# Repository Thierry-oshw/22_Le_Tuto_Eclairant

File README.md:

# 22_Le_Tuto_Eclairant

 mots clés: tutoriel led rgb éclairage diorama lighting

## Introduction

Les LEDs sont utilisables pour un diorama. Elles présentent comme avantages:
    1. De ne pas chauffer (en tout cas moins qu’une ampoule si ça existe encore).
    2. D’être tellement vulgarisées et diffusées que leur coût est très faible.
    3. De fonctionner sous une faible tension (de l’ordre de 1,2V pour les LEDs classiques et 5V pour les RGBs)

Une LED RGB est la somme de 3 leds (Rouge, Verte, Bleue = Red Green Blue) pilotées par une petite puce qui va recevoir des instructions par une patte et les retransmettre par une autre pour la LED RGB suivante. Ce point va être détaillé par la suite.

Petite photo de famille :

En gros, LED classique = 2 pattes, LED RGB = 4 pattes.
Il y a aussi des LEDs classiques bicolores (il y a deux LEDs de couleurs différentes dans le même bulb). Mais je ne vais pas approfondir ce sujet là.

## Pilotage d’une LED classique

Il faut alimenter la LED classique avec une tension à ses bornes de 1,2V en général, et contrôler le courant qui y circule pour qu’il soit de l’ordre de 10mA (entre 5 et 20mA).
Plus le courant est fort, plus la luminosité est forte.
Pour obtenir ces conditions, le plus simple est de relier la LED classique à une source de tension via une résistance qui va limiter le courant et faire chuter la tension.

Et en gros, pour ceux qui s’en souvienne : u = R1 * i + u(diode)
U(diode) vaut approximativement 1,2V. Si i vaut 5mA, il faut les couples suivants tension u et résistance R1 (je suis sympa, je vous fais un tableau avec des valeurs normalisées).

|u|i|
|-|:-|
|1,5V (pile AAA cylindrique par exemple)|68 Ohms|
|3,3V|470 Ohms|
|5V|820 Ohms|

Les résistances devront avoir un boîtier permettant de dissiper au moins 50mW.
ATTENTION : toujours mettre une résistance sinon ça va mal finir pour la LED. (il y a une façon de faire pour ne pas mettre de résistance mais il faut alors piloter la LED en courant, c’est pas simple).

## Pilotage LED RGB

Il y a plusieurs fabricants de LED RGBs avec bien sûr des différences. Je sais faire fonctionner des LEDs WS2812B (et apparentés). Donc je vous parle de celles-ci.

Là, la LED a besoin d’une tension 5V sur les pattes 1 (VDD au plus) et 3 (VSS au moins).
La patte DIN reçoit les ordres pour les 3 couleurs pour elle-même ou la suivante via sa patte DOUT.
Les LEDS sont à la queue-leu-leu (daisy chain en anglais).

Une méthode pour les piloter est alors d’utiliser par exemple une carte Arduino Nano avec 3 potentiomètres par exemple :

Et on utilise le bouton pour régler l'intensité lumineuse.

Les potentiomètres sont dédiées chacun à l'intensité d'une couleur.

La brillance de l'ensemble est réglée par un bouton. Un appui long fait augmenter la valeur jusqu'à un max et retombe à zéro.

Le code arduino est dans le répertoire: Le_Tuto_Eclairant_SW de ce projet.
J'ai utilisé Visual Studio Code avec platform IO. Vous pouvez utilisez à la place l'IDE arduino, vous avez juste à recopier le fichier main dans:
\Le_Tuto_Eclairant_SW\Le_Tuto_Eclairant_SW\src\main.cpp
et le renommer en .ino ou le coller dans un projet Arduino.

Le code est très simple. (Je n'ai même pas mis de debounce sur le bouton..)

Le projet kicad est dans le répertoire: Le_Tuto_Eclairant_HW.
J'utilise encore Kicad version 5, j'ai pas encore migré.

Les fichiers pour la fabrication du PCB sont dans le répertoire: Le_Tuto_Eclairant_HW\dossier_fabrication
Ils sont prêts pour être fabriqué chez JLCPCB.COM. (C'est un exemple).

Quelques photos du résultat:

En espérant que cela puisse vous permettre de réaliser un diorama avec la lumière qui vous plait.

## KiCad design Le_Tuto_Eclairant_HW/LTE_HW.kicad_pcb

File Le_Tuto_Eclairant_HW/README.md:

# Le_Tuto_Eclairant_HW
 Hardware du Tuto éclairant.

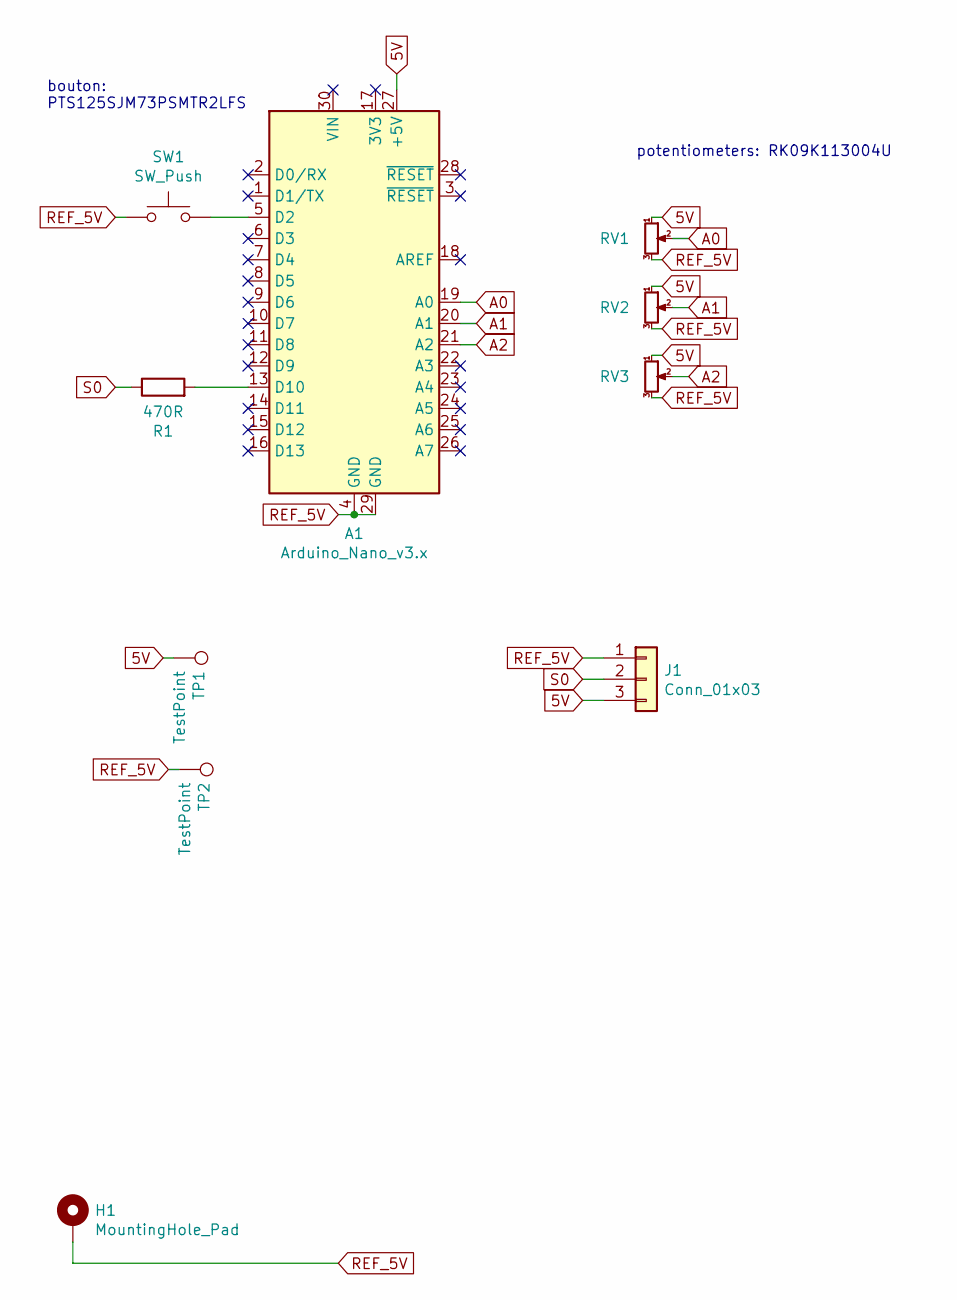
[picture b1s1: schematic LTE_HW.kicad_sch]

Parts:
A1: Arduino_Nano_v3.x; Arduino_Nano
H1: MountingHole_Pad; MountingHole_3.2mm_M3_Pad_Via
J1: Conn_01x03; JST_XH_S3B-XH-A_1x03_P2.50mm_Horizontal
R1: 470R; R_0603_1608Metric_Pad1.05x0.95mm_HandSolder
RV1, RV2, RV3: R_Potentiometer_Small; Potentiometer_Alps_RK09K_Single_Vertical
SW1: SW_Push; SW_Push_1P1T_NO_CK_PTS125Sx43PSMTR
TP1, TP2: TestPoint; PinHeader_1x01_P2.54mm_Vertical

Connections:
5V: A1.27 (+5V), J1.3, RV1.1, RV2.1, RV3.1, TP1.1
A0: A1.19 (A0), RV1.2
A1: A1.20 (A1), RV2.2
A2: A1.21 (A2), RV3.2
unnamed: A1.5 (D2), SW1.2
unnamed: A1.13 (D10), R1.2
REF_5V: A1.4 (GND), A1.29 (GND), H1.1, J1.1, RV1.3, RV2.3, RV3.3, SW1.1, TP2.1
S0: J1.2, R1.1

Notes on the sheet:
bouton: PTS125SJM73PSMTR2LFS
potentiometers: RK09K113004U

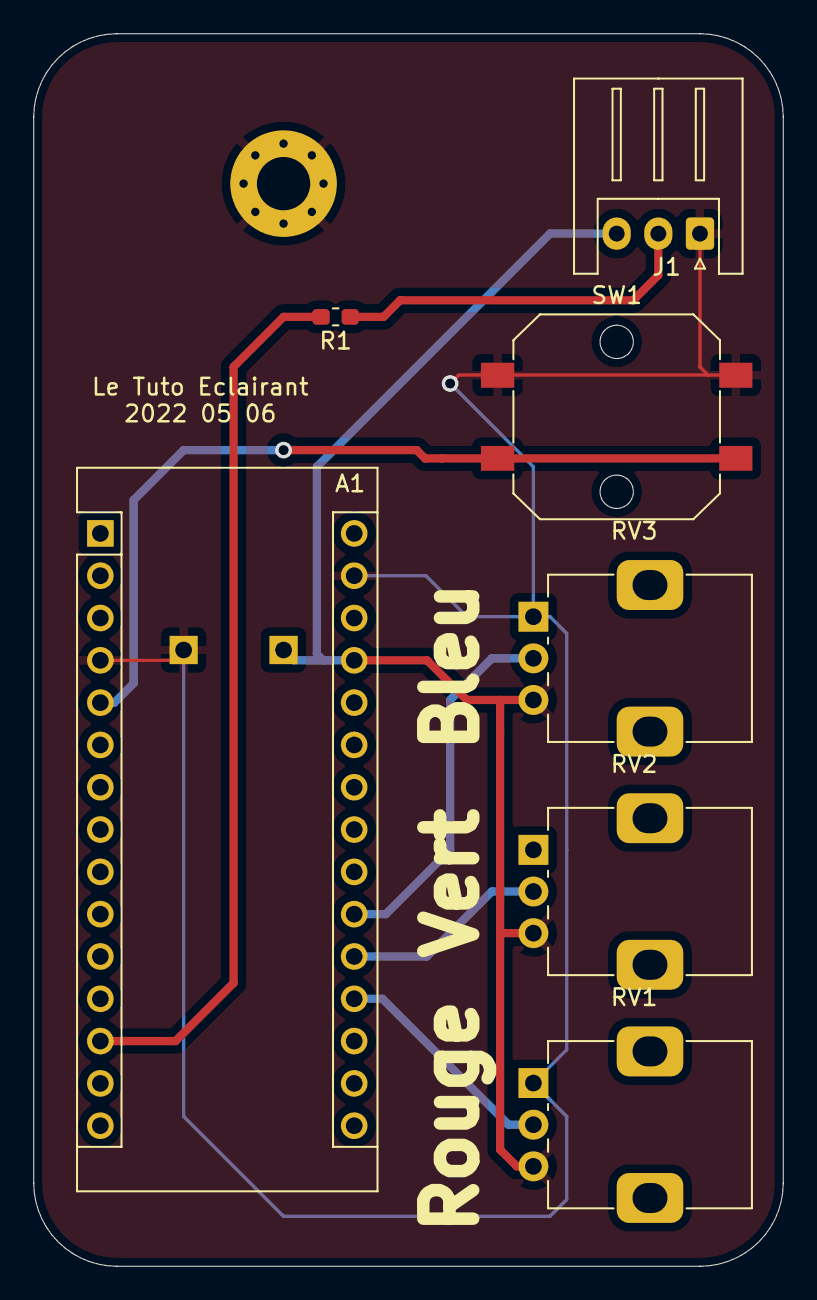
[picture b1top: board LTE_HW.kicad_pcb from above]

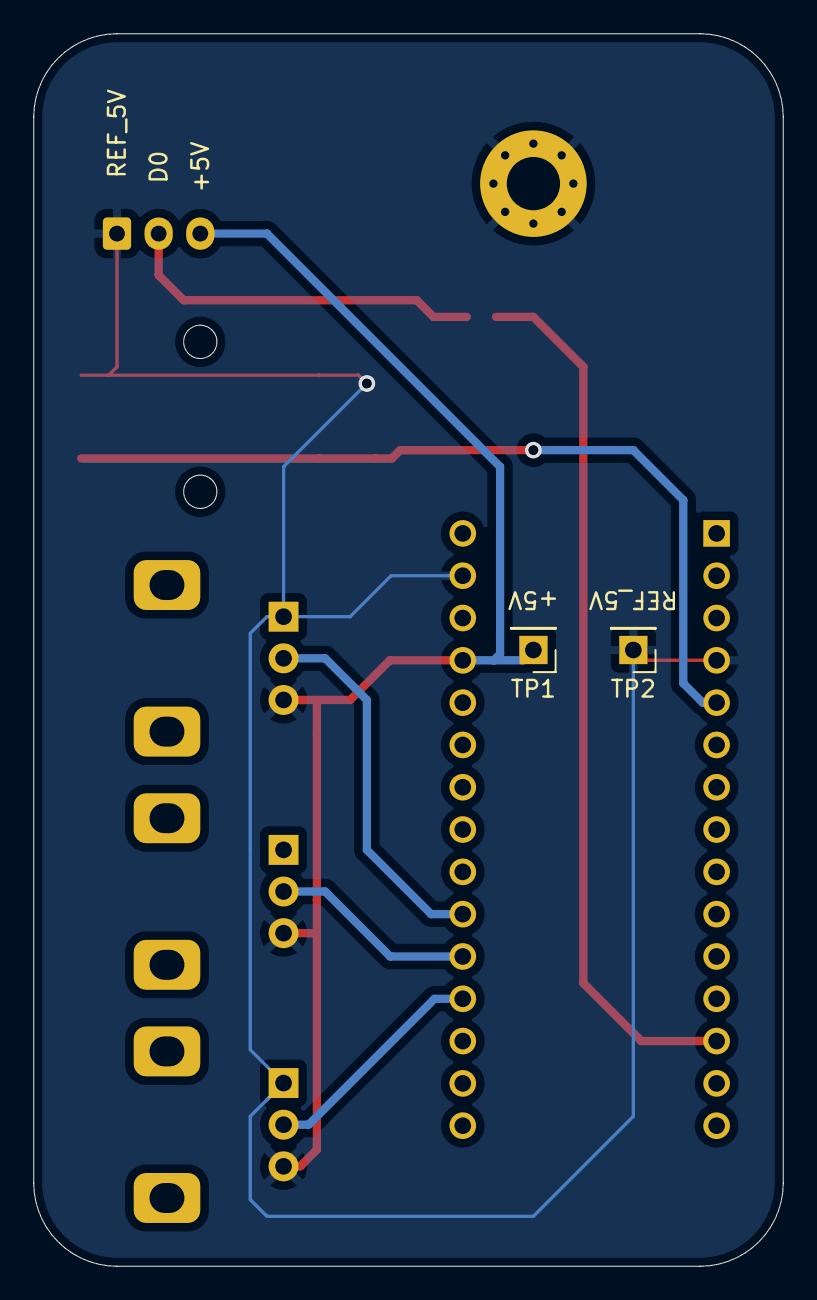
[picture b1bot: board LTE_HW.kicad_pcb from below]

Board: 2 copper layers, 45.0 x 74.0 mm, 10 parts (2 on the bottom side), 8 nets.

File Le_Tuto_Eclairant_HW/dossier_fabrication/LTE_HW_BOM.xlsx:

Comment | Designator | Footprint | LCSC Part #（optional）
JST_XH_S3B | J1 | JST_XH_S3B | C18428
470R | R1 | R_0603 | C23179
Push button | SW1 | button | C411882
Pot Alps RK09K | RV1,RV2,RV3 | potentiometer | C202382

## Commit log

2022-05-06 init and done
2022-05-06 suppression H2 à H3
2022-05-06 coché option "monté en surface"
    pour apparition dans fichier position
2022-05-06 coché option pour J1
    pour apparaitre dans fichier de placement
2022-05-06 dossier fabrication
2022-05-28 MAJ README
2022-07-30 Premier jet
2022-07-30 Ajout bouton control brillance ultra simple
2022-07-30 maj du readme pour présentation du projet.
2023-01-01 passage à kicad 6
